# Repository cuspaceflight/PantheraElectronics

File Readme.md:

# PANTHERA
Software for the Panthera electronics.

PCB contains a LORA RA-02, MPU6050, BMP280, UBLOX MAX-m8q GPS, and Teensy 4.2

The software is designed to report some data over LORA while logging as much information as possible to the internal SD card.

## Build instructions
### IDE
The Arduino IDE should be able to run and build the project

### Manual
Dependencies
```sh
arduino-cli
teensy-loader-cli
minicom
make
```

Arduino libraries
```sh
neogps
adafruit_bmp280
adafruit_mpu6050
lora
```

Ensure the port in the Makefile is set correctly

To build there is either
```sh
make build
make upload
```
Where upload will also upload to the teensy board.

```sh
make listen
```
Will start listening on the serial port

## TESTS
The Tests folder includes a list of files that when compiled test individual components of the PCB

These tests can be conditionally compiled by settings the relevant flags within PantheraSoftware.ino

While the tests are designed for this PCB they should be useable for any other board will small modifications

These tests ensure correct running of each of the components to track down
any broken components

## Notes
The reason behind the name source instead of src is due to arduino-cli including
any files either in the base directory, or files includes in src. This leads to
double inclusion of Main.cpp if header guards are not used which I chose to
avoid, hence the odd naming of the folder

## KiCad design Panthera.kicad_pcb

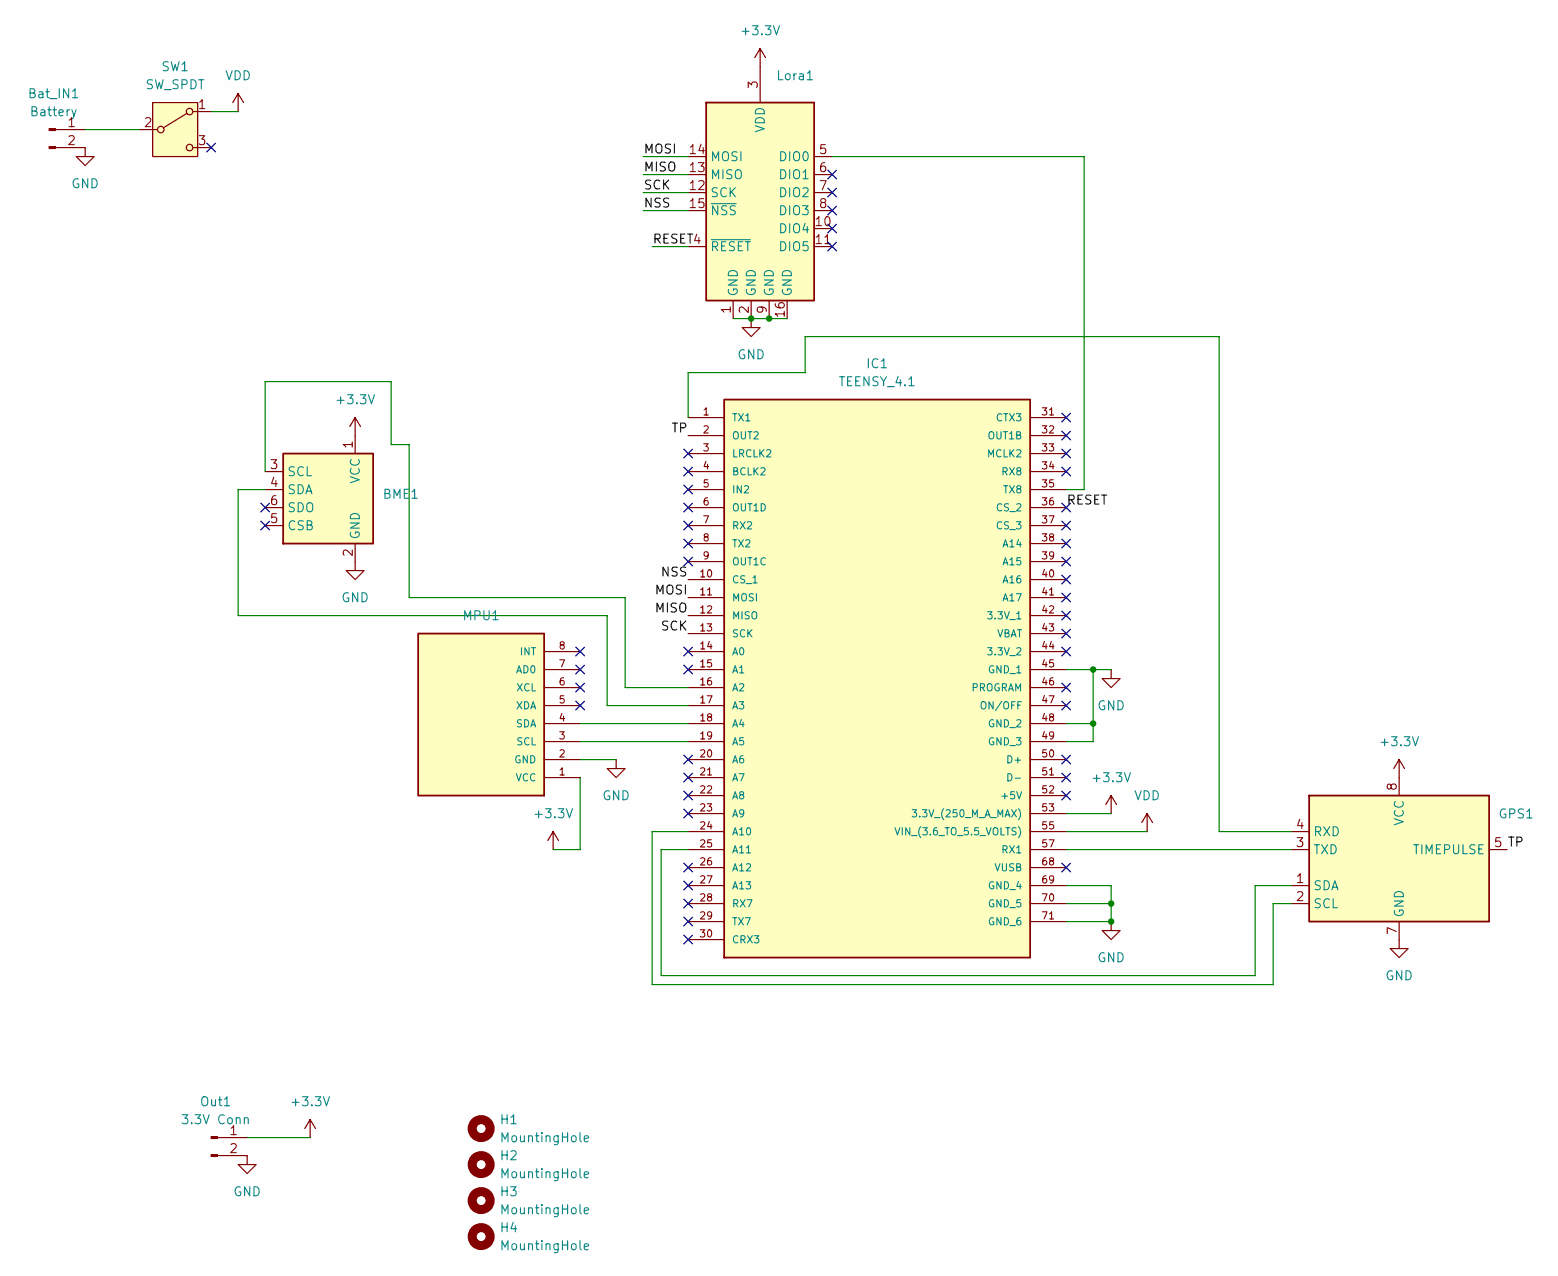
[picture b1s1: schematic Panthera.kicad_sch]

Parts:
BME1: BMP280 breakout board
Bat_IN1: Battery; PinHeader_1x02_P2.54mm_Vertical
GPS1: MAX-M8Q-0-10 breakout board
H1, H2, H3, H4: MountingHole; MountingHole_2.2mm_M2
IC1: TEENSY_4.1; TEENSY41; Manufacturer_Part_Number TEENSY 4.1
Lora1: Ai Thinker Ra-02 breakout board
MPU1: GY-521; MPU6050
Out1: 3.3V Conn; PinHeader_1x02_P2.54mm_Vertical
SW1: SW_SPDT; SK-12D07

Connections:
+3.3V: BME1.1 (VCC), GPS1.8 (VCC), IC1.53 (3.3V_(250_M_A_MAX)), Lora1.3 (VDD), MPU1.1 (VCC), Out1.1
/MISO: IC1.12 (MISO), Lora1.13 (MISO)
/MOSI: IC1.11 (MOSI), Lora1.14 (MOSI)
/NSS: IC1.10 (CS_1), Lora1.15 (~NSS)
/RESET: IC1.36 (CS_2), Lora1.4 (~RESET)
/SCK: IC1.13 (SCK), Lora1.12 (SCK)
/TP: GPS1.5 (TIMEPULSE), IC1.2 (OUT2)
GND: BME1.2 (GND), Bat_IN1.2, GPS1.7 (GND), IC1.45 (GND_1), IC1.48 (GND_2), IC1.49 (GND_3), IC1.69 (GND_4), IC1.70 (GND_5), IC1.71 (GND_6), Lora1.1 (GND), Lora1.2 (GND), Lora1.9 (GND), Lora1.16 (GND), MPU1.2 (GND), Out1.2
unnamed: BME1.3 (SCL), IC1.16 (A2)
unnamed: BME1.4 (SDA), IC1.17 (A3)
unnamed: Bat_IN1.1, SW1.2 (B)
unnamed: GPS1.4 (RXD), IC1.1 (TX1)
unnamed: GPS1.2 (SCL), IC1.24 (A10)
unnamed: GPS1.1 (SDA), IC1.25 (A11)
unnamed: GPS1.3 (TXD), IC1.57 (RX1)
unnamed: IC1.18 (A4), MPU1.4 (SDA)
unnamed: IC1.19 (A5), MPU1.3 (SCL)
unnamed: IC1.35 (TX8), Lora1.5 (DIO0)
VDD: IC1.55 (VIN_(3.6_TO_5.5_VOLTS)), SW1.1 (A)

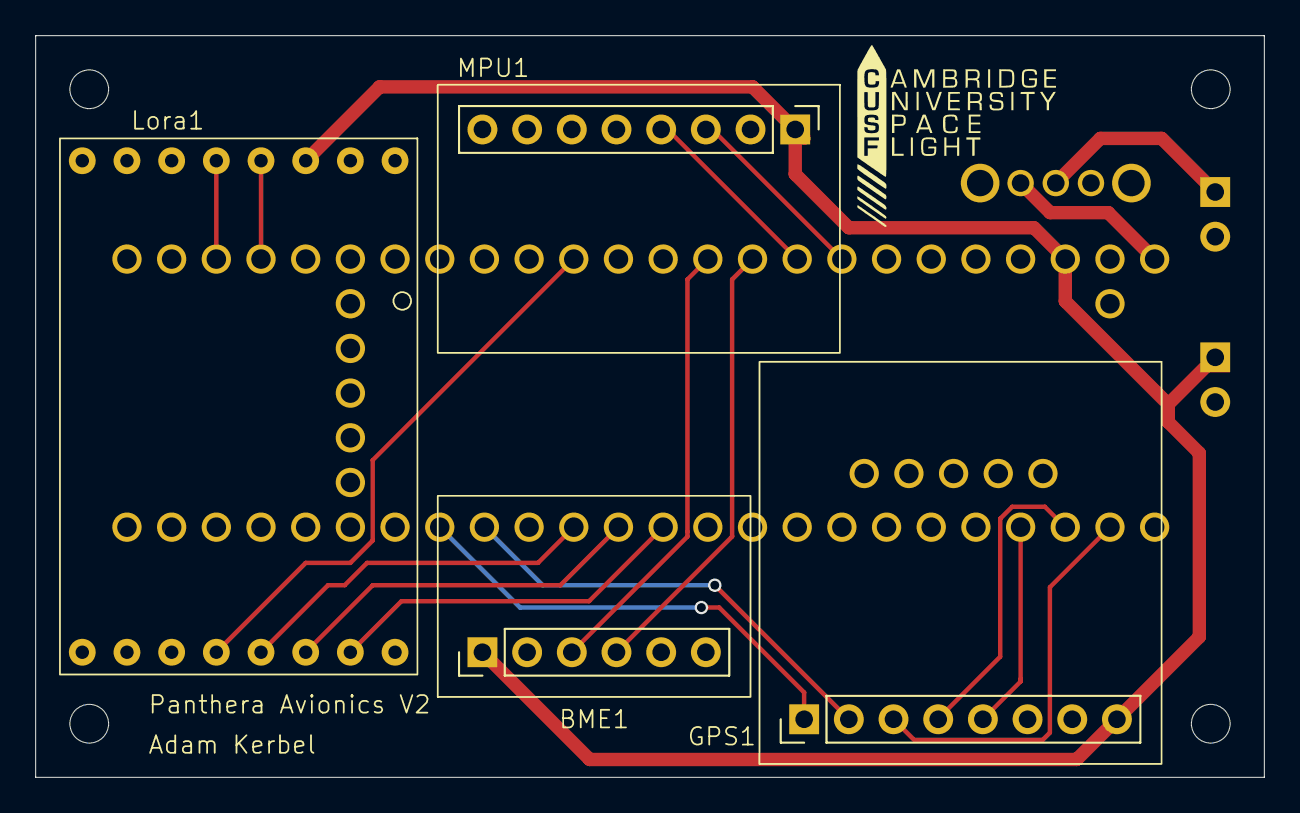
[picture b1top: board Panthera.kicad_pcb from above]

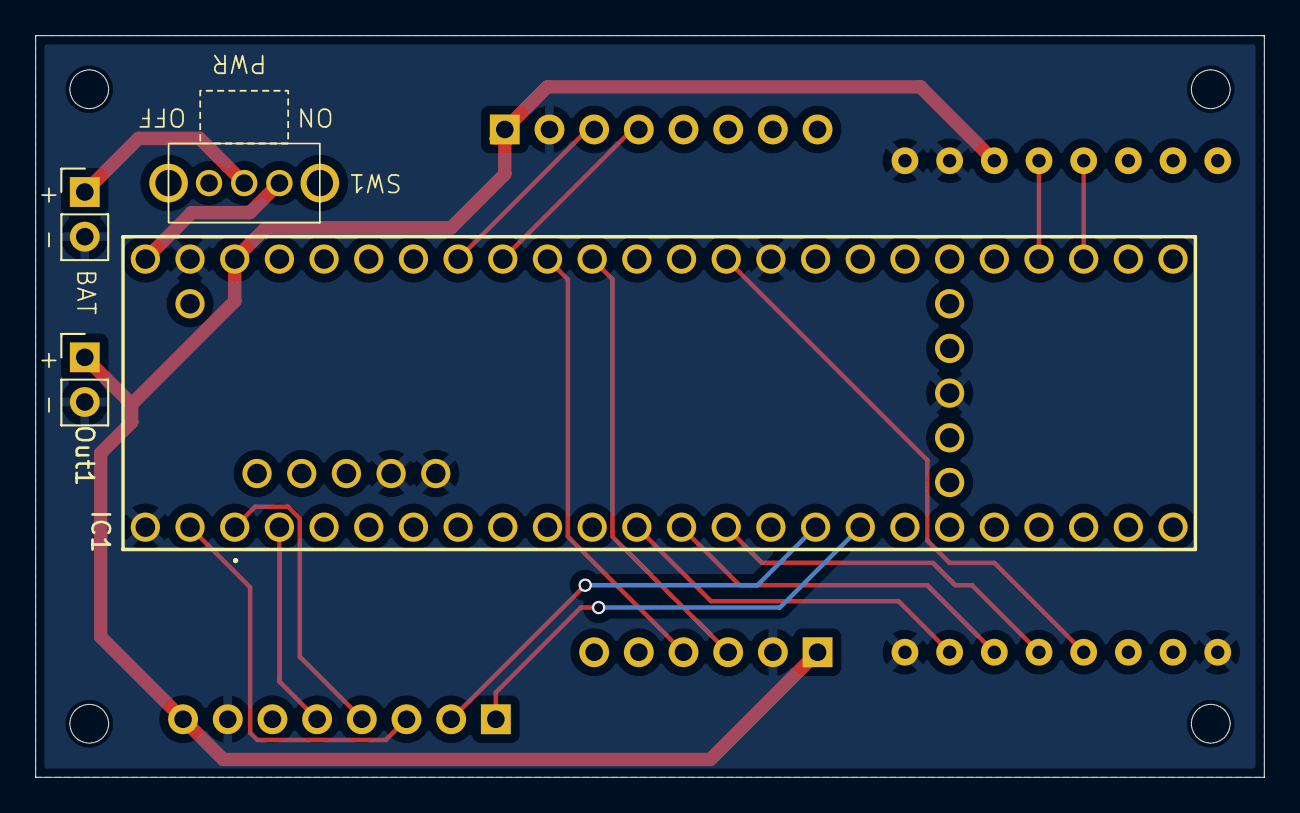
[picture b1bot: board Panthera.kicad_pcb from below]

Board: 2 copper layers, 69.9 x 42.2 mm, 12 parts (4 on the bottom side), 19 nets.

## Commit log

2025-02-09 Initial PCB
2025-02-09 Updated PCB
2025-05-21 Initial project Tests implemented for individual components
2025-05-22 Working Makefile and basic code
2025-05-25 Updated files
2025-05-26 Updated file structure
2025-06-21 Updated code to start representing the actual flow of information during the flight
2025-06-22 Updated code to include GPS logging and lora transmission
2025-07-05 Fixed SD card code
2025-07-24 Basic passing of messages
2025-07-24 Working Receiver code
2025-07-24 Updated Avionics
2025-09-13 Modified LoRa send code to work with ground stations
